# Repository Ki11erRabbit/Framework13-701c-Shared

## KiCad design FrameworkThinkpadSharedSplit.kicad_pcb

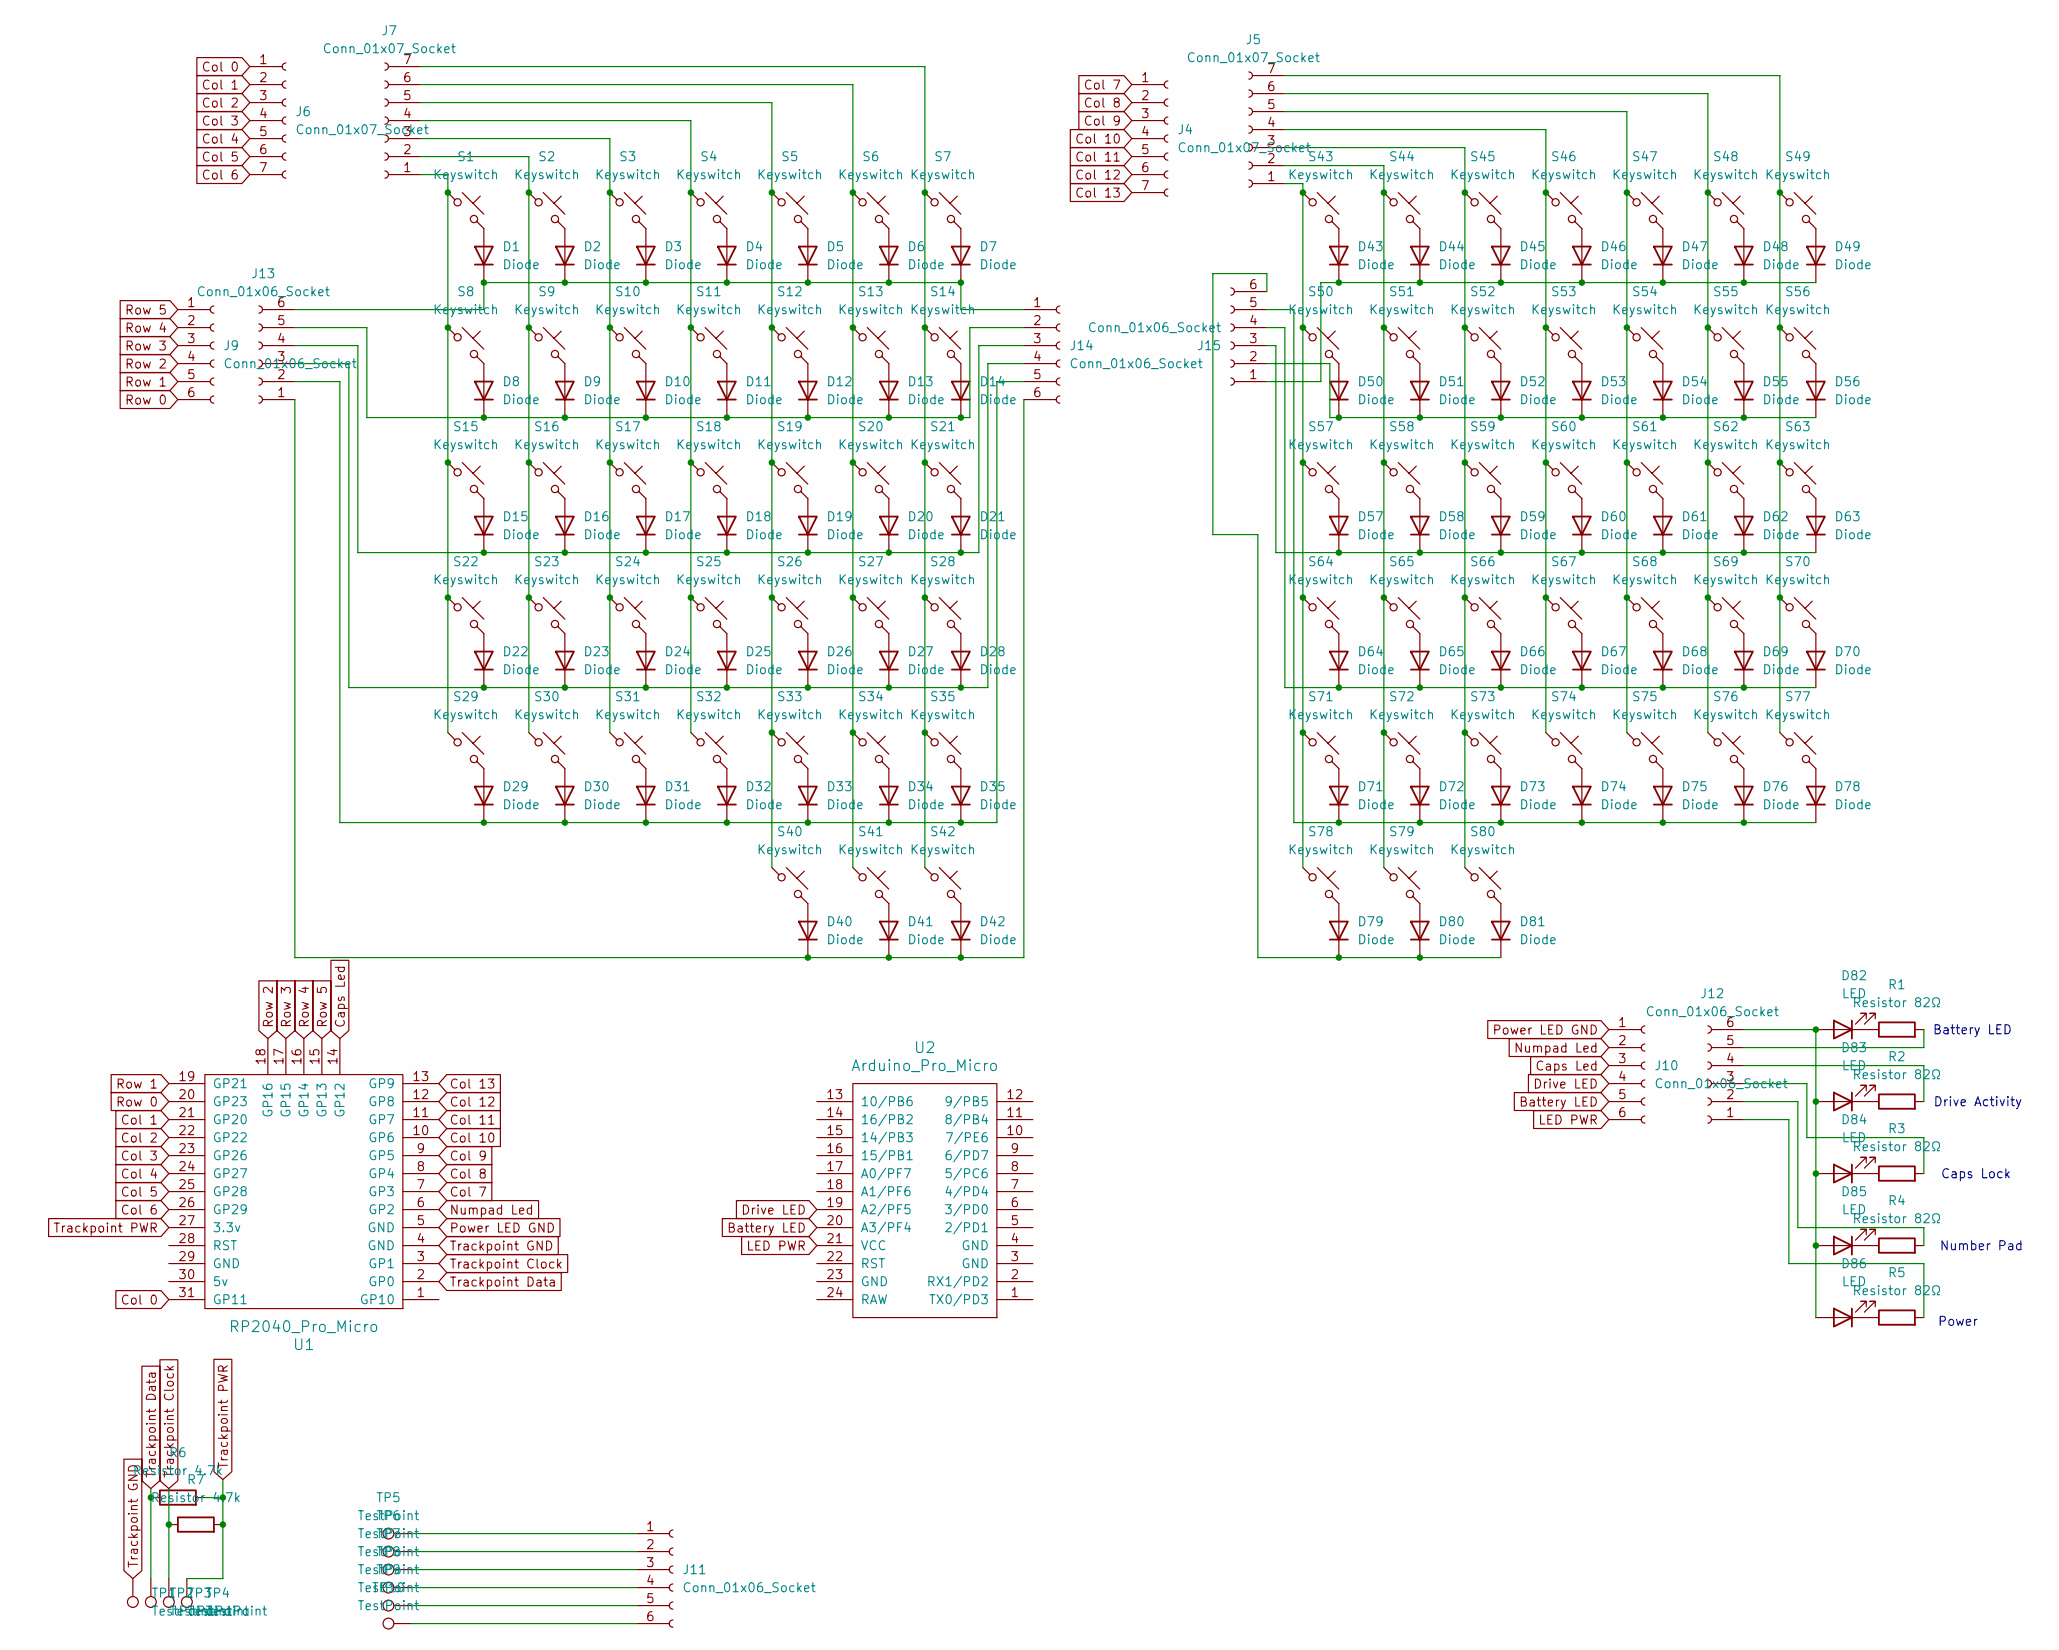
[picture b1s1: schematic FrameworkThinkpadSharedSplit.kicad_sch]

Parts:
D1, D2, D3, D4, D5, D6, D7, D8, D9, D10, D11, D12, D13, D14, D15, D16, D17, D18, D19, D20, D21, D22, D23, D24, D25, D26, D27, D28, D29, D30, D31, D32, D33, D34, D35, D40, D41, D42, D43, D44, D45, D46, D47, D48, D49, D50, D51, D52, D53, D54, D55, D56, D57, D58, D59, D60, D61, D62, D63, D64, D65, D66, D67, D68, D69, D70, D71, D72, D73, D74, D75, D76, D78, D79, D80, D81: Diode; Diode_SOD-123
D82, D83, D84, D85, D86: LED; LED_D5.0mm
J4, J5, J6, J7: Conn_01x07_Socket; Molex_PicoBlade_53048-0710_1x07_P1.25mm_Horizontal
J9, J10, J11, J12, J13, J14, J15: Conn_01x06_Socket; Molex_PicoBlade_53048-0610_1x06_P1.25mm_Horizontal
R1, R2, R3, R4, R5: Resistor 82Ω; R_Axial_DIN0207_L6.3mm_D2.5mm_P7.62mm_Horizontal
R6, R7: Resistor 4.7k; Resistor_1206
S1, S2, S3, S4, S5, S6, S7, S8, S9, S10, S11, S12, S13, S14, S15, S16, S17, S18, S19, S20, S21, S22, S23, S24, S25, S26, S27, S28, S29, S30, S31, S32, S33, S34, S35, S40, S41, S42, S43, S44, S45, S46, S47, S48, S49, S50, S51, S52, S53, S54, S55, S56, S57, S58, S59, S60, S61, S62, S63, S64, S65, S66, S67, S68, S69, S70, S71, S72, S73, S74, S75, S76, S77, S78, S79, S80: Keyswitch; Choc_V1V2_1.00u
TP1, TP2, TP3, TP4, TP5, TP6, TP7, TP8, TP9, TP10: TestPoint; SolderWirePad_1x01_SMD_1x2mm
U1: RP2040_Pro_Micro
U2: Arduino_Pro_Micro

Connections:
Battery LED: J10.5, U2.20 (A3/PF4)
Caps Led: J10.3, U1.14 (GP12)
Col 0: J6.1, U1.31 (GP11)
Col 1: J6.2, U1.21 (GP20)
Col 2: J6.3, U1.22 (GP22)
Col 3: J6.4, U1.23 (GP26)
Col 4: J6.5, U1.24 (GP27)
Col 5: J6.6, U1.25 (GP28)
Col 6: J6.7, U1.26 (GP29)
Col 7: J4.1, U1.7 (GP3)
Col 8: J4.2, U1.8 (GP4)
Col 9: J4.3, U1.9 (GP5)
Col 10: J4.4, U1.10 (GP6)
Col 11: J4.5, U1.11 (GP7)
Col 12: J4.6, U1.12 (GP8)
Col 13: J4.7, U1.13 (GP9)
Drive LED: J10.4, U2.19 (A2/PF5)
LED PWR: J10.6, U2.21 (VCC)
unnamed: D1.2 (A), S1.2
unnamed: D1.1 (K), D2.1 (K), D3.1 (K), D4.1 (K), D5.1 (K), D6.1 (K), D7.1 (K), J13.6, J14.1
unnamed: D2.2 (A), S2.2
unnamed: D3.2 (A), S3.2
unnamed: D4.2 (A), S4.2
unnamed: D5.2 (A), S5.2
unnamed: D6.2 (A), S6.2
unnamed: D7.2 (A), S7.2
unnamed: D8.2 (A), S8.2
unnamed: D9.2 (A), S9.2
unnamed: D10.2 (A), S10.2
unnamed: D8.1 (K), D9.1 (K), D10.1 (K), D11.1 (K), D12.1 (K), D13.1 (K), D14.1 (K), J13.5, J14.2
unnamed: D11.2 (A), S11.2
unnamed: D12.2 (A), S12.2
unnamed: D13.2 (A), S13.2
unnamed: D14.2 (A), S14.2
unnamed: D15.2 (A), S15.2
unnamed: D15.1 (K), D16.1 (K), D17.1 (K), D18.1 (K), D19.1 (K), D20.1 (K), D21.1 (K), J13.4, J14.3
unnamed: D16.2 (A), S16.2
unnamed: D17.2 (A), S17.2
unnamed: D18.2 (A), S18.2
unnamed: D19.2 (A), S19.2
unnamed: D20.2 (A), S20.2
unnamed: D21.2 (A), S21.2
unnamed: D22.2 (A), S22.2
unnamed: D22.1 (K), D23.1 (K), D24.1 (K), D25.1 (K), D26.1 (K), D27.1 (K), D28.1 (K), J13.3, J14.4
unnamed: D23.2 (A), S23.2
unnamed: D24.2 (A), S24.2
unnamed: D25.2 (A), S25.2
unnamed: D26.2 (A), S26.2
unnamed: D27.2 (A), S27.2
unnamed: D28.2 (A), S28.2
unnamed: D29.2 (A), S29.2
unnamed: D29.1 (K), D30.1 (K), D31.1 (K), D32.1 (K), D33.1 (K), D34.1 (K), D35.1 (K), J13.2, J14.5
unnamed: D30.2 (A), S30.2
unnamed: D31.2 (A), S31.2
unnamed: D32.2 (A), S32.2
unnamed: D33.2 (A), S33.2
unnamed: D34.2 (A), S34.2
unnamed: D35.2 (A), S35.2
unnamed: D40.2 (A), S40.2
unnamed: D40.1 (K), D41.1 (K), D42.1 (K), J13.1, J14.6
unnamed: D41.2 (A), S41.2
unnamed: D42.2 (A), S42.2
unnamed: D43.2 (A), S43.2
unnamed: D43.1 (K), D44.1 (K), D45.1 (K), D46.1 (K), D47.1 (K), D48.1 (K), D49.1 (K), J15.1
unnamed: D44.2 (A), S44.2
unnamed: D45.2 (A), S45.2
unnamed: D46.2 (A), S46.2
unnamed: D47.2 (A), S47.2
unnamed: D48.2 (A), S48.2
unnamed: D49.2 (A), S49.2
unnamed: D50.2 (A), S50.2
unnamed: D50.1 (K), D51.1 (K), D52.1 (K), D53.1 (K), D54.1 (K), D55.1 (K), D56.1 (K), J15.2
unnamed: D51.2 (A), S51.2
unnamed: D52.2 (A), S52.2
unnamed: D53.2 (A), S53.2
unnamed: D54.2 (A), S54.2
unnamed: D55.2 (A), S55.2
unnamed: D56.2 (A), S56.2
unnamed: D57.2 (A), S57.2
unnamed: D57.1 (K), D58.1 (K), D59.1 (K), D60.1 (K), D61.1 (K), D62.1 (K), D63.1 (K), J15.3
unnamed: D58.2 (A), S58.2
unnamed: D59.2 (A), S59.2
unnamed: D60.2 (A), S60.2
unnamed: D61.2 (A), S61.2
unnamed: D62.2 (A), S62.2
unnamed: D63.2 (A), S63.2
unnamed: D64.2 (A), S64.2
unnamed: D64.1 (K), D65.1 (K), D66.1 (K), D67.1 (K), D68.1 (K), D69.1 (K), D70.1 (K), J15.4
unnamed: D65.2 (A), S65.2
unnamed: D66.2 (A), S66.2
unnamed: D67.2 (A), S67.2
unnamed: D68.2 (A), S68.2
unnamed: D69.2 (A), S69.2
unnamed: D70.2 (A), S70.2
unnamed: D71.2 (A), S71.2
unnamed: D71.1 (K), D72.1 (K), D73.1 (K), D74.1 (K), D75.1 (K), D76.1 (K), D78.1 (K), J15.5
unnamed: D72.2 (A), S72.2
unnamed: D73.2 (A), S73.2
unnamed: D74.2 (A), S74.2
unnamed: D75.2 (A), S75.2
unnamed: D76.2 (A), S76.2
unnamed: D78.2 (A), S77.2
unnamed: D79.2 (A), S78.2
unnamed: D79.1 (K), D80.1 (K), D81.1 (K), J15.6
unnamed: D80.2 (A), S79.2
unnamed: D81.2 (A), S80.2
unnamed: D82.2 (A), D83.2 (A), D84.2 (A), D85.2 (A), D86.2 (A), J12.6
unnamed: D82.1 (K), R1.1
unnamed: D83.1 (K), R2.1
unnamed: D84.1 (K), R3.1
unnamed: D85.1 (K), R4.1
unnamed: D86.1 (K), R5.1
unnamed: J5.1, S43.1, S50.1, S57.1, S64.1, S71.1, S78.1
unnamed: J5.2, S44.1, S51.1, S58.1, S65.1, S72.1, S79.1
unnamed: J5.3, S45.1, S52.1, S59.1, S66.1, S73.1, S80.1
unnamed: J5.4, S46.1, S53.1, S60.1, S67.1, S74.1
unnamed: J5.5, S47.1, S54.1, S61.1, S68.1, S75.1
unnamed: J5.6, S48.1, S55.1, S62.1, S69.1, S76.1
unnamed: J5.7, S49.1, S56.1, S63.1, S70.1, S77.1
unnamed: J7.1, S1.1, S8.1, S15.1, S22.1, S29.1
unnamed: J7.2, S2.1, S9.1, S16.1, S23.1, S30.1
unnamed: J7.3, S3.1, S10.1, S17.1, S24.1, S31.1
unnamed: J7.4, S4.1, S11.1, S18.1, S25.1, S32.1
unnamed: J7.5, S5.1, S12.1, S19.1, S26.1, S33.1, S40.1
unnamed: J7.6, S6.1, S13.1, S20.1, S27.1, S34.1, S41.1
unnamed: J7.7, S7.1, S14.1, S21.1, S28.1, S35.1, S42.1
unnamed: J11.1, TP5.1
unnamed: J11.2, TP6.1
unnamed: J11.3, TP7.1
unnamed: J11.4, TP8.1
unnamed: J11.5, TP9.1
unnamed: J11.6, TP10.1
unnamed: J12.1, R5.2
unnamed: J12.2, R4.2
unnamed: J12.3, R3.2
unnamed: J12.4, R2.2
unnamed: J12.5, R1.2
Numpad Led: J10.2, U1.6 (GP2)
Power LED GND: J10.1, U1.5 (GND)
Row 0: J9.6, U1.20 (GP23)
Row 1: J9.5, U1.19 (GP21)
Row 2: J9.4, U1.18 (GP16)
Row 3: J9.3, U1.17 (GP15)
Row 4: J9.2, U1.16 (GP14)
Row 5: J9.1, U1.15 (GP13)
Trackpoint Clock: R7.1, TP3.1, U1.3 (GP1)
Trackpoint Data: R6.1, TP2.1, U1.2 (GP0)
Trackpoint GND: TP1.1, U1.4 (GND)
Trackpoint PWR: R6.2, R7.2, TP4.1, U1.27 (3.3v)

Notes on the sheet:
Power
Drive Activity
Caps Lock
Battery LED
Number Pad

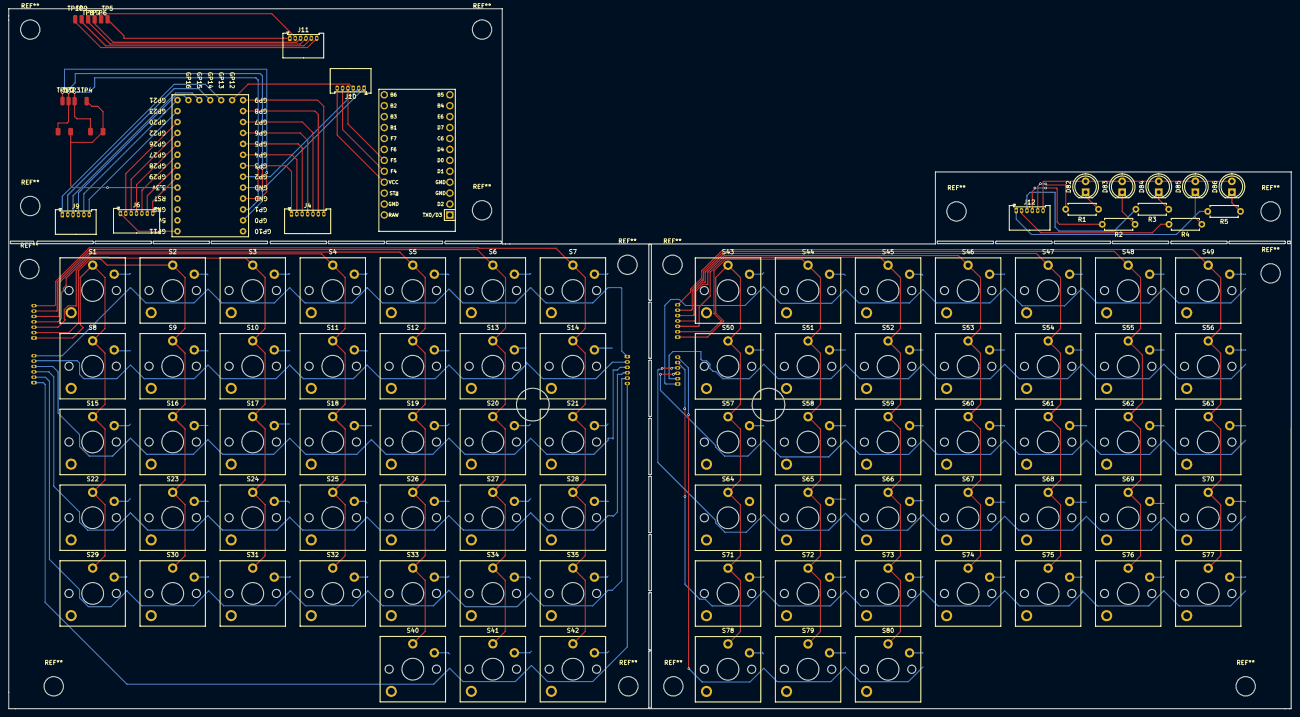
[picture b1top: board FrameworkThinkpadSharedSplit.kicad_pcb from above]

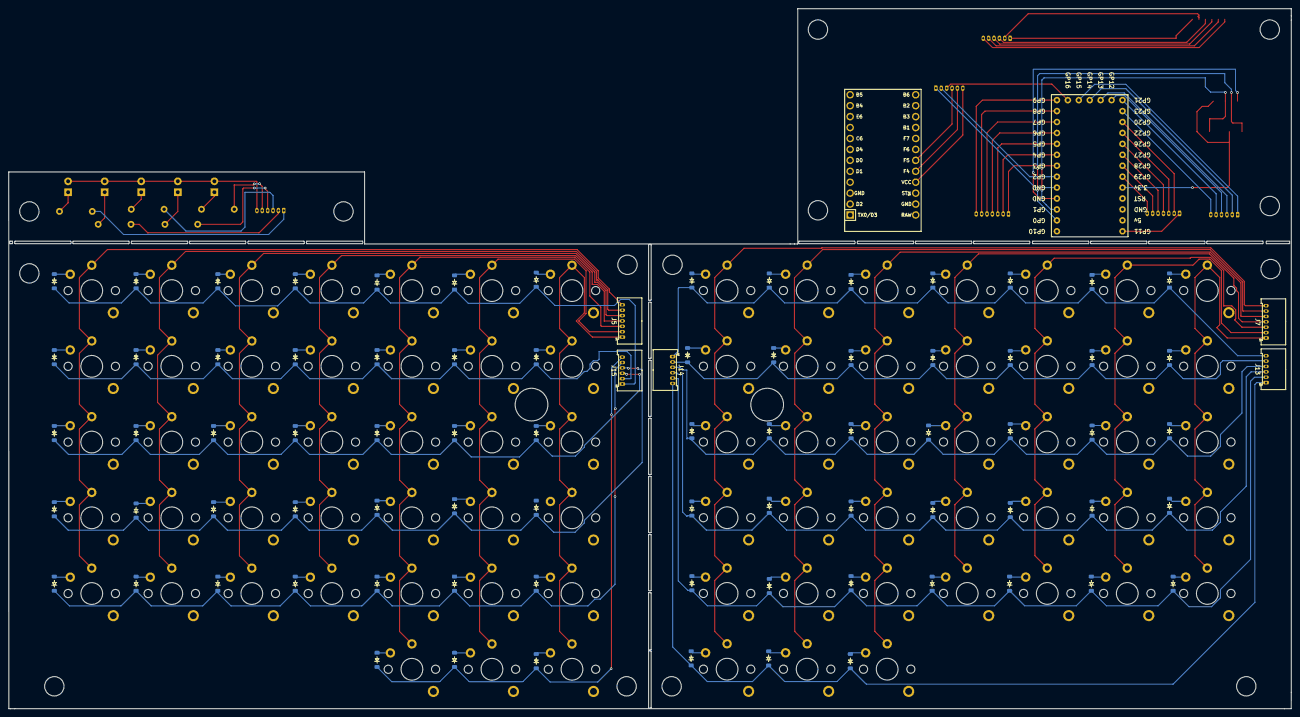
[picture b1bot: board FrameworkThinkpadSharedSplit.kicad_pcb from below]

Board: 2 copper layers, 298.1 x 162.7 mm, 187 parts (81 on the bottom side), 149 nets.

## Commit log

2025-03-09 added wiring to most parts
2025-03-09 moved pcbs around
2025-03-09 changed how board is connected to handle paneling
2025-03-11 updated pcb and added keycap stickers
2025-03-11 updated colors
2025-03-12 updated stickers
2025-03-16 added missing row and pullup resistors
2025-03-17 shrunk pcb down on the top and bottom
2025-03-18 adjusted positioning of trackpoint board
